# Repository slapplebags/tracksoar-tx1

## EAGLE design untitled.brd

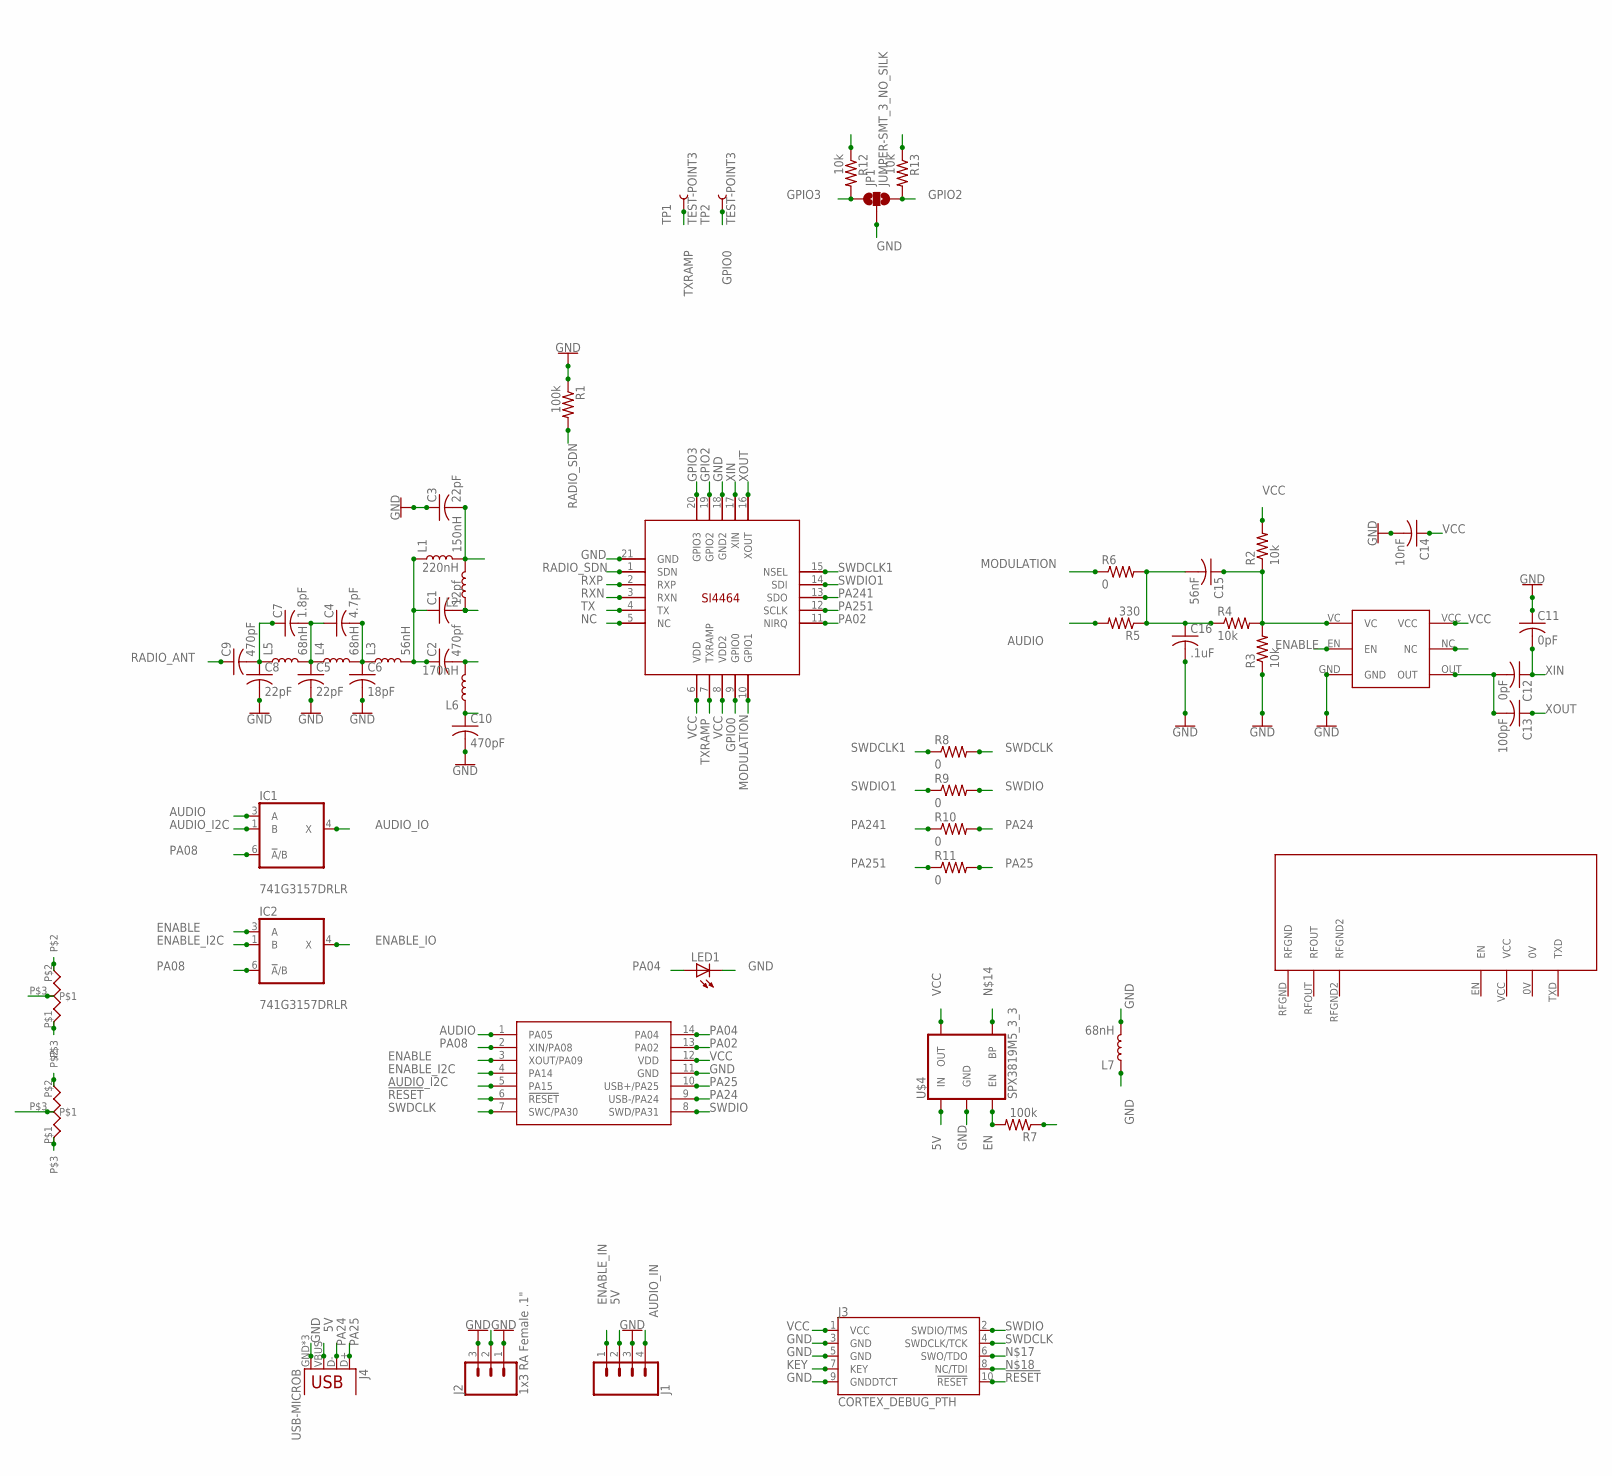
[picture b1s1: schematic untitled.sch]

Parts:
C1: 12pf; C0402K
C2: 470pf; C0402K
C3, C5, C8: 22pF; C0402K
C4: 4.7pF; C0402K
C6: 18pF; C0402K
C7: 1.8pF; C0402K
C9, C10: 470pF; C0402K
C11, C12: 0pF; C0402K
C13: 100pF; C0402K
C14: 10nF; C0402K
C15: 56nF; C0402K
C16: .1uF; C0402K
IC1, IC2: 741G3157DRLR; DRL_R-PDSO-N6
J1: CONN_04SMD_RA_FEMALE; 1X04_SMD_RA_FEMALE
J2: 1x3 RA Female .1"; 1X03_SMD_RA_FEMALE
J3: CORTEX_DEBUG_PTH; 2X5-PTH-1.27MM
J4: USB-MICROB
JP1: JUMPER-SMT_3_NO_SILK; SMT-JUMPER_3_NO_SILK
L1: 150nH; 0603
L2: 220nH; 0603
L3: 56nH; 0603
L4, L5, L7: 68nH; 0603
L6: 170nH; 0603
LED1: LEDCHIP-LED0603; CHIP-LED0603
R1, R7: 100k; R0402
R2, R3, R4, R12, R13: 10k; R0402
R5: 330; R0402
R6, R8, R9, R10, R11: 0; R0402
TP1, TP2: TEST-POINT3; PAD.03X.03
U$1: HC53BR-27; OSCILLATOR-SMD-7.5X5.2-6PIN
U$2: SI4464; QFN20+GNDPAD
U$3: SAMD11C14; SOIC14
U$4: SPX3819M5_3_3; SOT23-5
U$5, U$6: RM20A10K/20K
U$7: RADIOMETRIX-HX1

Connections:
5V: J1.2, J4.VBUS, R7.1, U$4.1 (IN)
!RESET: J3.10 (!RESET), U$3.6 (!RESET)
AUDIO: IC1.3 (A), R5.2, U$3.1 (PA05)
AUDIO_I2C: IC1.1 (B), U$3.5 (PA15)
AUDIO_IN: J1.4, U$6.P$1
AUDIO_IO: IC1.4 (X), U$6.P$3
EN: R7.2, U$4.3 (EN)
ENABLE: IC2.3 (A), U$1.EN, U$3.3 (XOUT/PA09)
ENABLE_I2C: IC2.1 (B), U$3.4 (PA14)
ENABLE_IN: J1.1, U$5.P$1
ENABLE_IO: IC2.4 (X), U$5.P$3
GND: C3.1, C5.2, C6.2, C8.2, C10.2, C11.1, C14.2, C16.2, IC1.2 (GND), IC2.2 (GND), J1.3, J2.1, J2.3, J3.3 (GND), J3.5 (GND), J3.9 (GNDDTCT), J4.GND, J4.MT1 (GND), J4.MT2 (GND), JP1.2, L7.1, L7.2, LED1.C, R1.1, R3.1, U$1.GND, U$2.18 (GND2), U$2.21 (GND), U$3.11 (GND), U$4.2 (GND), U$5.P$2, U$6.P$2
GPIO0: TP2.P$1, U$2.9 (GPIO0)
GPIO2: JP1.3, R13.2, U$2.19 (GPIO2)
GPIO3: JP1.1, R12.2, U$2.20 (GPIO3)
KEY: J3.7 (KEY)
MODULATION: R6.1, U$2.10 (GPIO1)
unnamed: C4.2, C6.1, L3.1, L4.2
unnamed: C1.1, C2.1, L1.1, L3.2
unnamed: C4.1, C5.1, C7.2, L4.1, L5.2
unnamed: C15.2, C16.1, R4.1, R5.1, R6.2
unnamed: C7.1, C8.1, C9.2, L5.1
unnamed: C15.1, R2.1, R3.2, R4.2, U$1.VC
NC: U$2.5 (NC)
OUT: C12.2, C13.2, U$1.OUT
PA02: U$2.11 (NIRQ), U$3.13 (PA02)
PA04: LED1.A, U$3.14 (PA04)
PA08: IC1.6 (!A!/B), IC2.6 (!A!/B), U$3.2 (XIN/PA08)
PA24: J4.D-, R10.2, U$3.9 (USB-/PA24)
PA25: J4.D+, R11.2, U$3.10 (USB+/PA25)
PA241: R10.1, U$2.13 (SDO)
PA251: R11.1, U$2.12 (SCLK)
RADIO_ANT: C9.1, J2.2
RADIO_SDN: R1.2, U$2.1 (SDN)
RXN: C1.2, L2.1, U$2.3 (RXN)
RXP: C3.2, L1.2, L2.2, U$2.2 (RXP)
SWDCLK: J3.4 (SWDCLK/TCK), R8.2, U$3.7 (SWC/PA30)
SWDCLK1: R8.1, U$2.15 (NSEL)
SWDIO: J3.2 (SWDIO/TMS), R9.2, U$3.8 (SWD/PA31)
SWDIO1: R9.1, U$2.14 (SDI)
TX: C2.2, L6.2, U$2.4 (TX)
TXRAMP: TP1.P$1, U$2.7 (TXRAMP)
VCC: C10.1, C14.1, IC1.5 (VCC), IC2.5 (VCC), J3.1 (VCC), L6.1, R2.2, R12.1, R13.1, U$1.VCC, U$2.6 (VDD), U$2.8 (VDD2), U$3.12 (VDD), U$4.5 (OUT)
XIN: C11.2, C12.1, U$2.17 (XIN)
XOUT: C13.1, U$2.16 (XOUT)

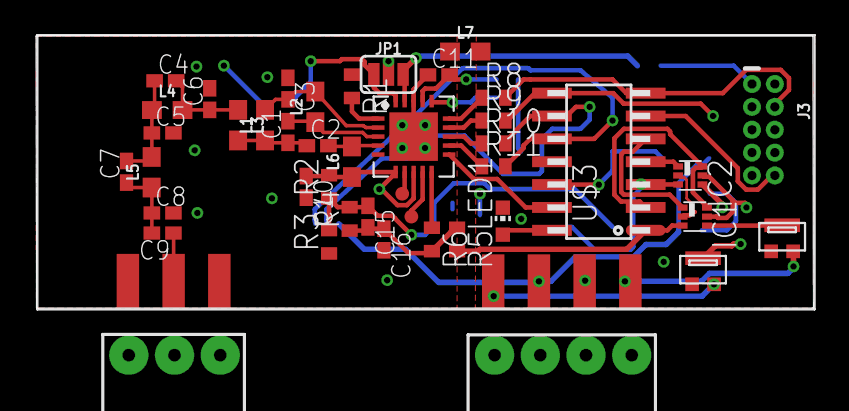
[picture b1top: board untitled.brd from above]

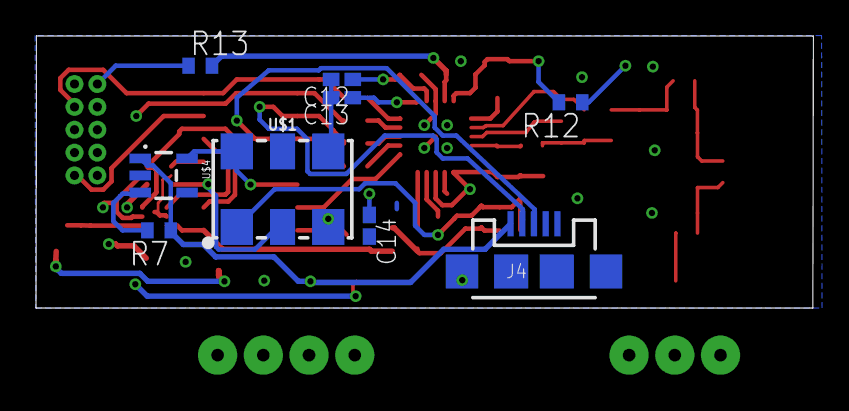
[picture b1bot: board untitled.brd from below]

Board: 4 copper layers, 43.2 x 15.1 mm, 53 parts (9 on the bottom side), 43 nets.

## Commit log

2018-02-02 Initial Schematic and routing
    put down most of the RF components and did a simple first pass at routing.
2018-02-03 initial atsamd21g schematic capture
    added samd21g connections.
2018-02-06 Added SAMD11C14
    second routing pass, moved to SAMD11C14 ARM processor
2018-02-09 Added USB connector
    added USB connector for debugging, dropped to 4 layer board
2018-02-10 Added test points to SI4464
    Added test points to unused pins for later use. Cleaned up routing.
2018-02-11 Added 0 ohm resistors to spi
    added 0 ohm jumpers between spi pins on the micro and si4464
2018-02-11 saving schematic
    eagle error due to inconsistency
2018-02-11 changed audio input path
    changed audio input to make the samd11c14 decode the audio and resend it to the VCO. Added fets to allow for i2c over enable and audio pins for future use.
2018-02-11 Updated USB routing
    cleaned up routing to USB connector
2018-02-20 RC1
    added 0805 resistor divider package for voltage level conversion of inputs. Final routing pass and verified DRC.
2018-04-22 Updated pin placements
    updated pin placements to their correct locations. Moved the ti switch to clear the 10 pin jtag header. adjusted board outline to correct size.

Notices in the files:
parts and their libraries:
SparkFun-Coils: Licensing: Creative Commons ShareAlike 4.0 International - https://creativecommons.org/licenses/by-sa/4.0
